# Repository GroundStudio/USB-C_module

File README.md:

GroundStudio USB-C module
====================================

Get it from [ardushop.ro](https://ardushop.ro/ro/home/1850-modul-usb-c-groundstudio.html)

Explore all the GroundStudio products at [GroundStudio.ro](https://groundstudio.ro/)

Description
-------------------
With this module you can finally incorporate a USB-C connector in your projects without having to solder each SMD pad.

Contents
-------------------

* [/Hardware](https://github.com/GroundStudio/USB-C_module/tree/main/Hardware) -- Schematics, layout.

Versions
-------------------
*(Not all tags shown)*

- [REV 1]

License
-------------------

This is released under the [Attribution-ShareAlike 4.0 International (CC BY-SA 4.0)](https://creativecommons.org/licenses/by-sa/4.0/) license.
**You are welcome to use this for commercial purposes.**

Please consider contributing back to this project or others to help the open-source hardware community continue to thrive and grow!

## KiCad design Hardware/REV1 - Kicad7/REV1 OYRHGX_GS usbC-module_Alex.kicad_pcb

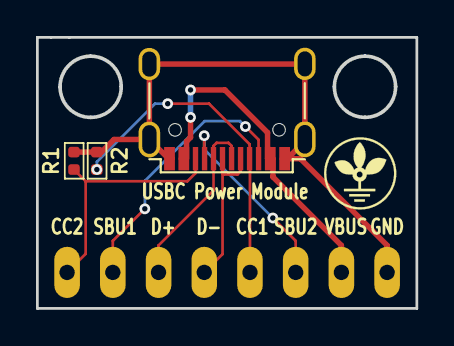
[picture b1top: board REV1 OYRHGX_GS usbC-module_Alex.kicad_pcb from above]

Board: 2 copper layers, 21.0 x 15.0 mm, 4 parts (0 on the bottom side), 8 nets.

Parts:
J1: Conn_01x08; PinHeader_1x08_P2.54mm_Vertical_Male
R1, R2: 5.1k; R_0402_1005Metric
USB1: USB_C_FULL; USB_C_C167321

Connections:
/CC1: J1.4, R2.2, USB1.A5
/CC2: J1.8, R1.2, USB1.B5
/D+: J1.6, USB1.A6, USB1.B6
/D-: J1.5, USB1.A7, USB1.B7
/GND: J1.1, R1.1, R2.1, USB1.0, USB1.A1, USB1.A12, USB1.B1, USB1.B12
/SBU1: J1.7, USB1.A8
/SBU2: J1.3, USB1.B8
/VBUS: J1.2, USB1.A4, USB1.A9, USB1.B4, USB1.B9

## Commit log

2024-03-15 - initial commit
